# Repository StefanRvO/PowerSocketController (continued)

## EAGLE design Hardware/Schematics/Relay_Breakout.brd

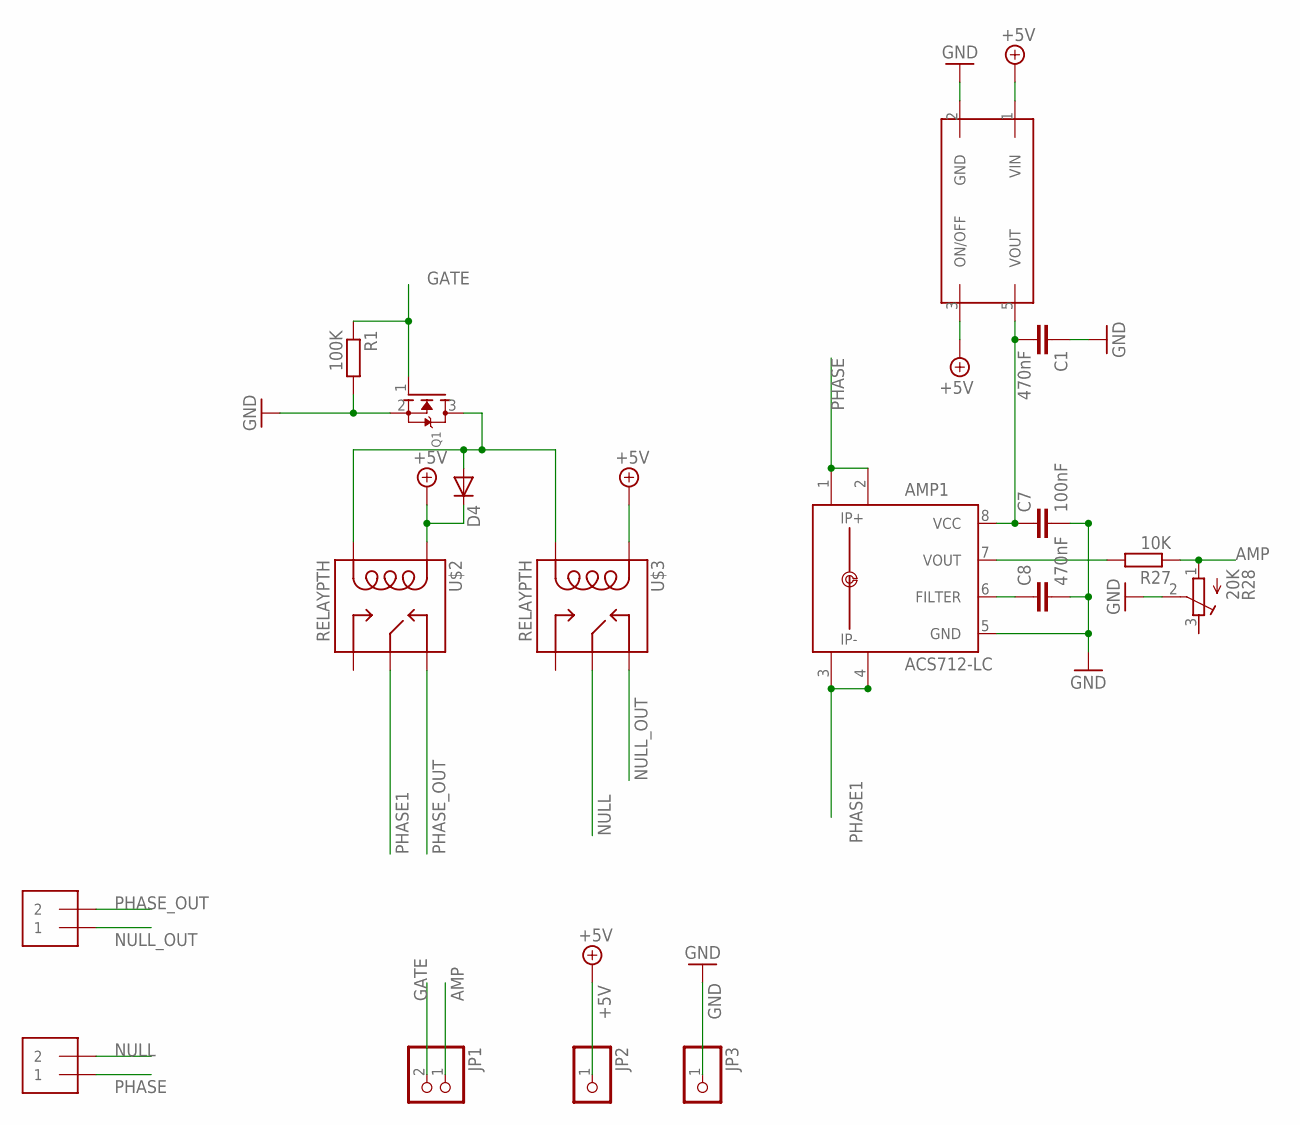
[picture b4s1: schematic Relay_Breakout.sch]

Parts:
4.5V_REG: S1112; SOT23-5
AMP1: ACS712-LC; SOIC8
C1, C8: 470nF; C0805
C7: 100nF; C0805
D4: DIODE-DO-214AC; DO-214AC
J1, J2: 1X2-3.5MM
JP1: PINHD-1X2; 1X02
JP2, JP3: PINHD-1X1; 1X01
Q1: MOSFET-NREFLOW; SOT23
R1: 100K; R0805
R27: 10K; R0805
R28: 20K; RTRIM5X
U$2, U$3: RELAYPTH; SRD-05VDC-SL-C

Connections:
4.5V: 4.5V_REG.5 (VOUT), AMP1.8 (VCC), C1.2, C7.1
+5V: 4.5V_REG.1 (VIN), 4.5V_REG.3 (ON/OFF), D4.C, JP2.1, U$2.COIL1, U$3.COIL1
AMP: JP1.1, R27.1, R28.1 (A)
GATE: JP1.2, Q1.1 (G), R1.1
GND: 4.5V_REG.2 (GND), AMP1.5 (GND), C1.1, C7.2, C8.2, JP3.1, Q1.2 (S), R1.2, R28.2 (S)
unnamed: D4.A, Q1.3 (D), U$2.COIL0, U$3.COIL0
unnamed: AMP1.6 (FILTER), C8.1
unnamed: AMP1.7 (VOUT), R27.2
NULL: J1.2, U$3.SWCOMMON
NULL_OUT: J2.1, U$3.SWCLOSED (SWCLOSE)
PHASE: AMP1.1 (IP+), AMP1.2 (IP+1), J1.1
PHASE1: AMP1.3 (IP-), AMP1.4 (IP-1), U$2.SWCOMMON
PHASE_OUT: J2.2, U$2.SWCLOSED (SWCLOSE)

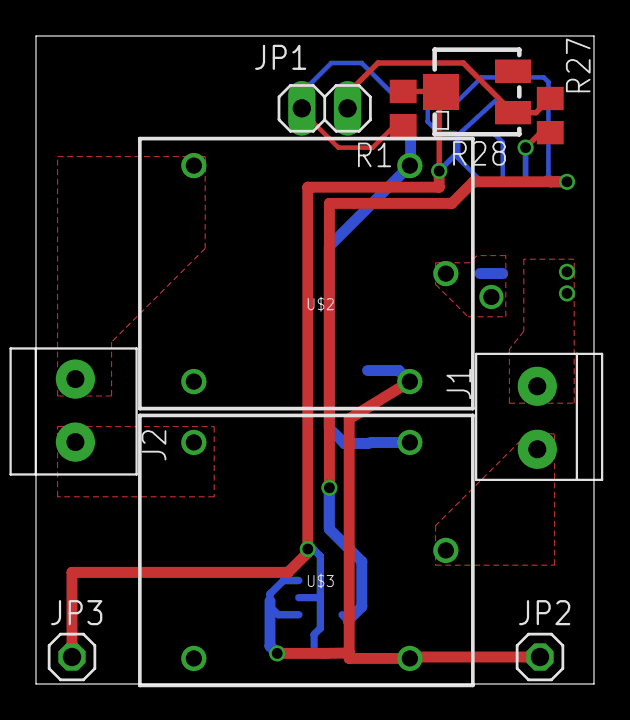
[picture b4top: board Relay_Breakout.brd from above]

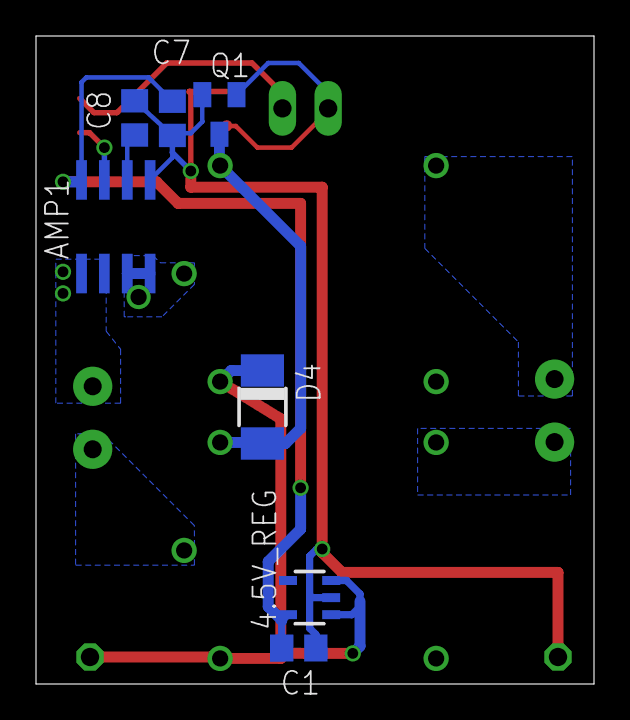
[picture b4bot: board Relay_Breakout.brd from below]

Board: 2 copper layers, 31.0 x 36.0 mm, 17 parts (7 on the bottom side), 13 nets.

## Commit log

2016-08-18 Initial Commit TODO: Change lwip API usage to use sockets.
2016-08-19 Changed the implementation to use the socket based API. Seems a lot more stable. Still not able to handle to many connections at the same time, especially if they have high traffic.
2016-08-19 Started to implement support for saving settings. They are saved on files in an spiffs filesystem. Currently reads settings for ssid and password from the filesystem. There seems to be a bug which ma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
    Started implementing support for ota updates.
2016-08-23 Made Sepperated functionality into seperate classes Suppor for more saved settings
2016-09-12 Added stuff for httpserver, unstable.
    Added schematics. Boardlayout not done.
2016-09-13 Updated schematic to use for a 3 slot device.
    Some routing still remaining.
2016-09-16 Added 3d file.
2016-09-17 Changed dimension to 50mmx100mm and routed the board
2016-09-17 Schematic changes: Added JTAG pins. Changed some resistors to 0805 type. Only use 3 holes for the buttons. Changed current sensor to 3.3V tolerant ACS710. Some rewiring needed on board.
2016-09-18 Did some routing of the board.
2016-09-18 Routed board.
2016-09-18 Some Routing improvements.
2016-09-18 Added GND planes.
2016-09-18 Added more clearance to GND planes.
2016-09-18 Run AC traces on both sides.
2016-09-18 Further routing improvements.
2016-09-19 Added mounting holes.
2016-09-22 New board layout
2016-09-22 Added .brd script.
2016-09-25 Changed amp-meters and added 5V step-up. I probably don't have the correct package.
2016-09-25 Changed package for triac.
2016-09-25 Fixed error in wiring of voltage divider.
2016-10-27 Fixed triac wiring.
2016-10-27 Changed resistor values.
2016-10-30 Replaced triacs with realys Replaced ESP3212 with ESP-12S
2016-10-30 Small edits.
2016-10-31 Made relay and amperemeter breakout board.
2016-10-31 fixed some issues in relay breakout.
2016-11-01 Routed power socket board.
2016-11-02 Added panelising readme and lua file.
2016-11-02 Added relay breakout panelizing config.
2016-11-02 Updated powersocket config.
2016-11-20 Added voltage regulators to both boards. Removed solder mask en 220V traces.
2016-11-20 Removed some pullups, as the ESP support this in hardware.
2017-02-06 Updated software to esp32.
2017-02-06 Added initial infrastructure for running a http server (using Mongoose).
2017-02-06 Added spiffs submodule for serving files from html.
2017-02-06 Further attempts on submodule.
2017-02-06 Cleaned up submodules
2017-02-06 hopefully final fix.
2017-02-07 Implemented filesystemhandler which initilize the spiffs filesystem on flash, and registers it with espressif's vfs system. This also means that you need to have mkspiffs installed.
2017-02-07 mongoose __should__ now serve files from the filesystem.
2017-02-07 Spiffs filesystem seems to be working correctly now. Mongoose also works, but serving files from the filesystem is not fully tested yet.
2017-02-07 Small changes.
2017-02-08 VFS filesystem listing is now working (using code from the mongoose-os esp32 port).
2017-02-08 Changed to another implementation of vfs for spiffs, where there is no problems with functions such at stat. Mongoose can now serve files from the filesystem.
2017-02-08 Some mongoose configs. Still can't get it to compile with ssl support.
2017-02-09 SSL now works. It does however seem a bit slow, and also uses a lot of memery... Should probably be investigated.
2017-02-09 Added define to mongoose makefile to get around mbedTLS bug.
2017-02-12 Added html files.
2017-02-14 Many improvements: Utilize ssi to perform include operations in html files (this make it possible to have a common header/menu/etc. for each page, and prevents duplication). OTA upgrade is implemente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
2017-02-15 Fixed a bug in settingshandler Make a http GET request for / redirect to /index.shtml
2017-02-16 Many edits. Added template for a settings page. Added template for Current measurer WiFi AP and STA settings are now (mostly) loaded from NVS storage.
2017-03-07 Multiple aditions. SSID names can now be set from the web interface. Status page added. password and username added, but can't be changed atm.
2017-03-07 fixed some bugs and added more options.
2017-03-07 Added a reset option in the reboot page.
2017-03-08 Added page with switches etc.
2017-03-08 Switch toggles new sends one, and only one post key-value pair on both on and off click.
2017-03-09 Added "Skeleton"
2017-03-09 More progress on switchhandler.. Not tested.
2017-03-10 Changed to a theme which is better for small screens. Changed to smaller versions of jquery and bootstrap. You can now actually toggle the relay using the buttons on the page. The state is remembered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
2017-03-10 Some layout stuff.
2017-03-10 Begun work on migrating to PureCSS instead of bootstrap.
2017-03-11 Most pages uses purecss now. Still need to get toggles to behave nicely.
2017-03-11 Switches almost working.
2017-03-12 index on master: 15d93b0 Switches almost working.
2017-03-16 Some bugfixes
2017-03-16 Started using jquery to update stuff on the webpage, send reponses in json.
2017-03-16 changed mongoose remote
2017-03-16 Removed mongoose remote (for later re-adding)
2017-03-16 Only page which still needs to be converted into jquery is settings.
2017-03-17 Fixed Settings page..
2017-03-19 Some bugfixes and preparation for changing username and password.
2017-03-23 Attempt at setting up Travis Continuous integration
2017-03-23 Set up continuos integration with Travis CI.
2017-03-23 Added release on tag
2017-03-23 Try to fix deploy.
2017-03-29 Avoid vias under the esp to make it easier to create the PCB ourself.
2017-04-02 Started implementing handling of button event. Code is not yet tested.
2017-04-02 More work on button and LED handling. Implementateted different LED modes for animations etc. Not tested yet.
2017-04-02 Some more work on LED blinking and button state handling.
2017-04-02 enabled pulldown
2017-04-02 Added new config options to sdkconfig.
2017-04-03 Set the pins for the PCB.
2017-04-03 Fixed bug in json code for switch state. Fixed bug in switchhandler where the timer was not started.
2017-04-03 Switch to using the LED PWM driver for controlling the button LED's, so we can now potentially do all kinds of fancy effects.
2017-04-04 Sampling ADC's using the hardware timer seems to be working correctly.
2017-04-07 Fixed ota upload More code for adc sampling and processing
2017-04-13 Implemented measuring of relay on and off bias. Still need to save the results to nvs.
2017-04-13 Save calibration to nvs and only recalibrate if no calibration is saved.
2017-04-13 Added json api for getting calibrations.
2017-04-13 Updated sdkconfig for new esp-idf options, and updated mkspiffs external version.
2017-04-14 Added page for showing the calibration More work on calibration infrastructure. !!!Not tested yet!!!
2017-04-14 Calibration seems to be working quite well now.
2017-04-14 Initial work on mDNS.
2017-04-18 Prevent timer interrupt for requiring flash access. some changeds in calibration structs. preparation for calibration on the go.
2017-04-18 Start of implementation of cookie based login manager.
2017-04-18 More work on live calibrations.
2017-06-05 Some work on implementing session-id based authentification.
2017-06-07 Work on LoginManager.
2017-06-08 Some work on Loginmanager Fixed a bug in computation of calibration standard deviation. Created schematic with relays on a seperate power supply, latched relays, and voltage measuring.
2017-06-08 Fixed some issues in the schematic.
2017-06-10 Elliptic curve cert.
2017-06-10 Some work on mdns.
2017-06-11 Try to save schematic for lower version of eagle.
2017-06-11 Working
2017-06-11 Fixed missing var
2017-06-11 Only create elements during first requests - else just update existing elements + hopefully works on iphone
2017-06-11 Took JS out - should fit into templates again
2017-06-12 Tasks.xml
2017-06-12 Added new 3D drawing.
2017-06-12 Fixed bug - is now tested with ESP32 module.
2017-06-13 Return OK in settings.
2017-06-15 Use jquery(ajax) to do post instead of default form.submittion
2017-06-15 Use jquery(ajax) to do post instead of default form.submittion. Changed http status code to 200.
2017-06-15 Remove includes....
2017-06-15 Missed includes
2017-06-16 Created new logicboard with isolation from HV side.
2017-06-16 Power board schematic mostly done.
2017-06-17 Relay board placement mostly done. Routing ~50% done.
2017-06-18 Power board routing done. Still missing adjustments of soldermask and silkscreen on both powerboard and logic board.
2017-06-18 Values and names fixed in silkscreen for powerboard. Slots added to powerboard.
2017-06-19 Made Logic Board a bit smaller.
2017-06-19 Work on changeing to FATFS. Not tested yet.
2017-06-19 Work on FAT32 migration.
2017-06-19 Fixed release bug.
2017-06-20 Migrated filesystem to FAT32.
2017-06-20 Increased number of filedescriptors.
2017-06-21 Updated board versions to final (v1) version, and added renders.
2017-06-21 Added some missing renders (actually the most important ones)
2017-07-03 Serving the get api now seems to be working, just need to actually serve the correct json response now. q# new file: components/zlib/win32/README-WIN32.txt
2017-07-03 All get API calls implemented.
2017-07-04 POST API implementation done. Only OTA missing. Will do that later.
2017-07-04 Removed mongoose dependencies.
2017-07-04 Removed mkspiffs dependency. Updated sdkconfig to newest esp-idf.
2017-07-04 Added dependency for libwebsockets to component.mk, so we compile in the right order.
2017-07-04 Fixed release.
2017-07-04 Split Http Server into multiple files.
2017-07-04 OTA Upgrade is working.
2017-07-05 Work on Authorisation and login session.
2017-07-06 Cookie based sessions are now enabled. Missing features: Unimplemented in frontend: Set current user password Delete an user Create an user Redirect to frontpage on successfull login Redirect to logi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
    Unimplemented in backend:
    List users
2017-07-07 Added tool for uploading over the air, and added a ota_flash command for make.
2017-07-09 Added PAge which shows hardware and software info
2017-07-09 Forgot some files.
2017-07-09 OTA Upgrades now require authentication.
2017-07-09 Added circular progress bar to OTA page.
2017-07-09 Some extra ota error checking. Added progress bar to make ota_flash
2017-07-09 Added popdown box to show actions Added Success page to show OTA upload successfull Added initial user page. Fixed some redirects.
2017-07-09 Added missing package to travis
2017-07-09 Added requirements file for OTAUploader, we need requests-toolbelt to show upload progress.
2017-07-09 Changes related to WiFi does not require a reboot anymore.
2017-07-11 The user can now change his password.
2017-07-11 You can now add and remove users.
2017-07-15 Implementation of PCF8574 driver and adaption of SwitchHandler to use it. Removed CurrentMeasurer, we will implement new stuff for the new IC's
    TODO: Implement support for new energy monitoring IC's
    Test drivers.
2017-07-17 Reading using the PCF8574 seems to work.
2017-07-19 Initialise hardware dependent on gpio and I2C addresses. Added argument to switchhandler to set wheter relays are active on or off. Work on CS5463 driver.
2017-07-19 Added initial document describing how hardware is versionised.
2017-07-19 SPI SCLK seems to be working.. Other lines not so much... Needs investigation.
2017-07-22 More work in CS5463 driver.
2017-07-22 More work on CS5463.
2017-07-22 Spi recieve seem to be working now!.
2017-07-24 Primarily work on CS5463 driver.
2017-07-24 Read registers based on the status register, and clear the status register bit after reading.
